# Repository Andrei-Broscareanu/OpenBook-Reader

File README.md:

# 📖 eBook Reader Portabil – ESP32-C6 Edition

Un eBook Reader cu consum redus, afișaj E-Ink și conectivitate modernă (Wi-Fi 6 & Bluetooth 5), construit în jurul microcontrollerului **ESP32-C6-WROOM-1-N8**.

---

## 🔧 Arhitectură Hardware

### 🧠 Microcontroller
- **ESP32-C6-WROOM-1-N8**
  - RISC-V core
  - Wi-Fi 6 și Bluetooth 5
  - Criptografie hardware integrată
  - Interfețe: SPI, I2C, GPIO

### 💾 Memorie
- **64MB NOR Flash** – W25Q512JVEIQ, conectată prin SPI
- **Slot microSD** – pentru stocare eBooks, conectat pe SPI separat

### 🔋 Alimentare
- **USB-C (PMF0501)** – intrare standard 5V
- **Protecție ESD (USBLC6-2SC6Y)** – pentru liniile USB
- **Încărcător Li-Po (MCP73831)** – pentru o celulă 3.7V, max 500mA
- **Baterie Li-Po 3.7V** – autonomie extinsă
- **Regulator LDO (MCP1700-3302E)** – convertește 5V la 3.3V

---

## 🖼️ Afișaj E-Ink

- Conector pentru ecrane de **1.54" E-Paper (200x200px)**
- Interfață: **SPI + GPIO**
- Circuit de alimentare:
  - Transistor Q3
  - Inductor L1
  - Diodă D2
- **Selector SJ1** – pentru tipul de display

---

## 📦 Periferice & Senzori

| Componentă        | Funcție                                | Interfață | Pini ESP32-C6         |
|-------------------|-----------------------------------------|-----------|------------------------|
| **BME688**        | Temperatură, umiditate, presiune, VOCs | I2C       | GPIO1 (SDA), GPIO2 (SCL) |
| **DS3231SN**      | RTC – ceas timp real                   | I2C       | GPIO1 (SDA), GPIO2 (SCL) |
| **MAX17048G-T10** | Fuel gauge baterie                     | I2C       | GPIO1 (SDA), GPIO2 (SCL) |
| **Buton Reset**   | Sistem reset                           | GPIO      | GPIO0                  |
| **Buton Boot**    | Bootloader                             | GPIO      | GPIO3                  |
| **Qwiic/Stemma QT**| Extensii rapide I2C                   | I2C       | GPIO1 (SDA), GPIO2 (SCL) |

---

## 🔌 Pini utilizați pe ESP32-C6

| Componentă       | Interfață     | Pini ESP32-C6             | Observații                |
|------------------|---------------|---------------------------|---------------------------|
| SD Card          | SPI           | GPIO10, GPIO11, GPIO12, GPIO13 | Bus SPI dedicat         |
| NOR Flash        | SPI           | GPIO6, GPIO7, GPIO8, GPIO9      | Bus SPI separat         |
| E-Ink Display    | SPI + GPIO    | GPIO18, GPIO19, GPIO20, GPIO21 | Control ecran           |
| Senzori + RTC    | I2C           | GPIO1 (SDA), GPIO2 (SCL)        | Comun I2C               |
| Butoane sistem   | GPIO          | GPIO0 (RST), GPIO3 (BOOT)       | Control utilizator      |
| Test Pads        | GPIO/UART     | GPIO17, GPIO22                   | Debug/UART              |

---

## ⚡ Estimare consum de energie

| Modul                    | Consum aproximativ         |
|--------------------------|----------------------------|
| ESP32-C6 activ           | ~80-100 mA                 |
| ESP32-C6 deep sleep      | ~10 µA                     |
| E-Ink refresh            | ~25 mA (temporar)          |
| SD Card idle / acces     | ~2 mA / ~50 mA             |
| RTC + BME688 standby     | ~3-5 µA                    |
| MAX17048                 | ~3 µA                      |

**Autonomie estimată cu baterie Li-Po 500mAh:**
- Utilizare normală: **15-20 ore**
- Standby (deep sleep): **până la câteva săptămâni**

---

## 🧩 Design PCB și carcasă

- Blocuri separate: alimentare, MCU, afișaj, senzori
- Plan de masă comun și trasee optimizate
- Conectori accesibili extern (USB, afisaj, butoane)
- Carcasă 3D ergonomică și compactă
- Randări 3D disponibile

---

## ✅ Status proiect

- [x] Hardware complet funcțional
- [x] PCB finalizat și validat
- [x] Carcasă 3D completă
- [x] Optimizare consum energetic
- [x] Conectivitate Wi-Fi 6 și Bluetooth 5

---

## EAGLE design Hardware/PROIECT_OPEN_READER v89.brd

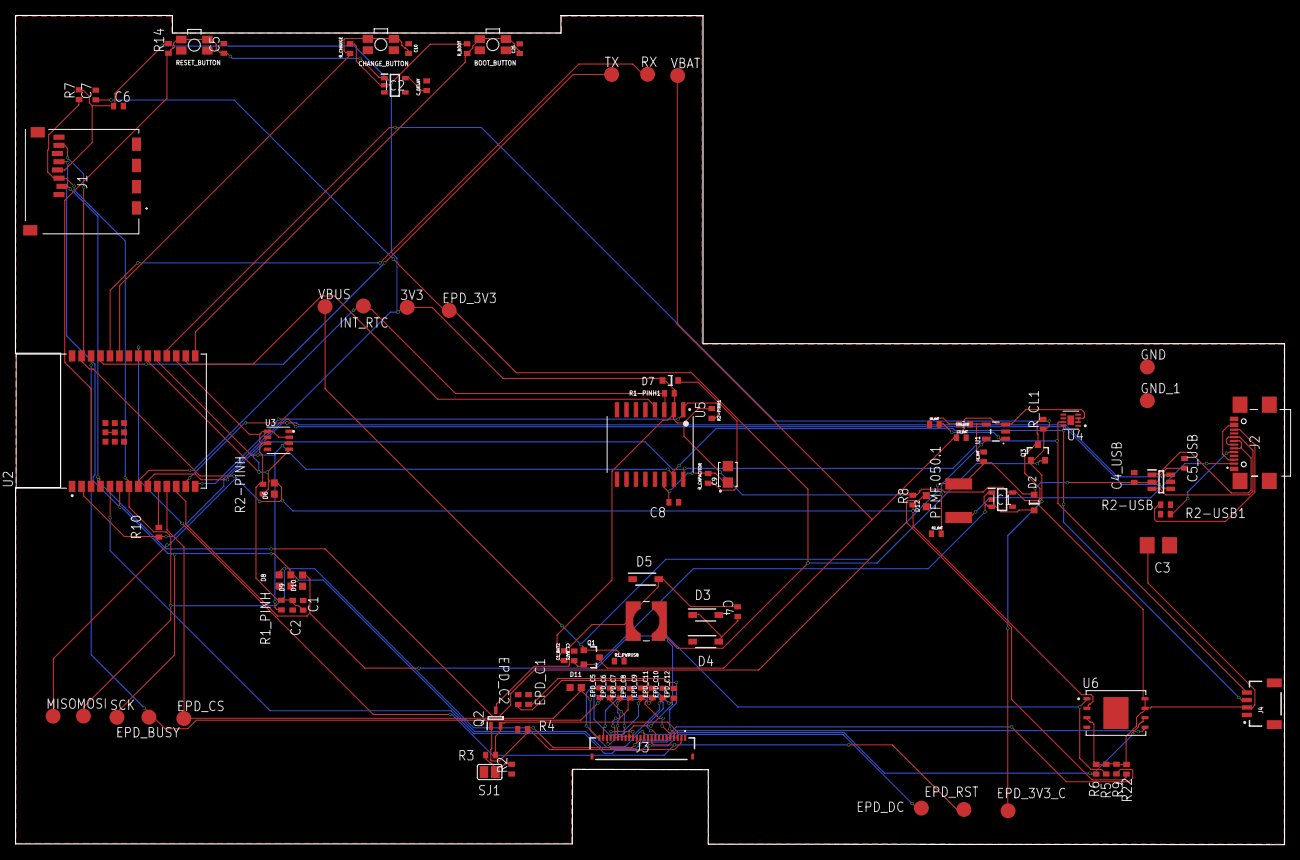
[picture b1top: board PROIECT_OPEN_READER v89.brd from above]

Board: 2 copper layers, 170.2 x 111.2 mm, 103 parts (0 on the bottom side), 57 nets.

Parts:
3V3: TPTP20R; TP20R
BOOT_BUTTON: BUTTON_CUSYOMV1; MYBUTTON
C1, C1_BAT1, C1_BAT2, C2: EAGLE-LTSPICE_C0402
C1_BAT, C2_BAT, C5_USB: 4.7uF; EAGLE-LTSPICE_C0402
C3: RCL_CT3528
C4: 4.7uF/25V; EAGLE-LTSPICE_C0402
C4_USB, C6, C8, C10, C25: 100nF; EAGLE-LTSPICE_C0402
C5: 1uF; EAGLE-LTSPICE_C0402
C7: 10uF; EAGLE-LTSPICE_C0402
C9: CPH3225A; CAPCP3225X100N
CHANGE_BUTTON: BUTTON_CUSYOMV1; MYBUTTON
CHG_LED: ADAFRUIT_CHIP-LED0603
C_DELAY: 100nF; EAGLE-LTSPICE_C0402
D1: USBLC6-2SC6Y; SOT95P280X145-6N
D2, D7: ESP32_WROVER_AVX---SD0805S020S1R0_AVX_SD0805S020S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; ESP32_WROVER_AVX---SD0805S020S1R0_AVX_SD0805S020S1R0_0
D3, D4, D5: MBR0530; SOD3716X135N
D6, D8, D9, D10, D11, D12: PGB1010603MR; DIOC1608X36N
EPD_3V3, EPD_3V3_C: TPTP20R; TP20R
EPD_BUSY: TPTP20R; TP20R
EPD_C1, EPD_C2, EPD_C6, EPD_C7, EPD_C8, EPD_C9, EPD_C10, EPD_C11, EPD_C12: 1uF/50V; EAGLE-LTSPICE_C0402
EPD_C5: 0.1uF/50V; EAGLE-LTSPICE_C0402
EPD_CS: TPTP20R; TP20R
EPD_DC: TPTP20R; TP20R
EPD_RST: TPTP20R; TP20R
GND: TPTP20R; TP20R
GND_1: TPTP20R; TP20R
IC1: XC6220A331MR-G; SOT95P280X120-5N
IC2: BD5229G-TR; SOT95P280X125-5N
INT_RTC: TPTP20R; TP20R
J1: 112A-TAAR-R03_ATTEND; 112ATAARR03ATTEND
J2: SAMACSYS_PARTS_USB4110-GF-A; SAMACSYS_PARTS_USB4110GFA
J3: FH34SRJ-24S-0.5SH_99_; FH34SRJ24S05SH99
J4: QWIIC_RIGHT_ANGLE; JST04_1MM_RA
L1: 68uH; IND_4828-WE-TPC_WRE
MISO: TPTP20R; TP20R
MOSI: TPTP20R; TP20R
PFMF.050.1: ESP32C6_VARISTOR_CT/CN1812
Q1, Q3: 20V/4.2A/52mΩ/1.4W; ESP32_WROVER_SPARKFUN-DISCRETESEMI_SOT23-3
Q2: SI1308EDL-T1-GE3; SOT65P210X110-3N
R1-PINH1, R1_PINH, R2-PINH, R2-PINH1, R4: 10K; ESP32_WROVER_EAGLE-LTSPICE_R0402
R1_BAT: 200; ESP32_WROVER_EAGLE-LTSPICE_R0402
R1_PWRUSB: 100K; ESP32_WROVER_EAGLE-LTSPICE_R0402
R2: 2.2; ESP32_WROVER_EAGLE-LTSPICE_R0402
R2-USB: 5K1; ESP32_WROVER_EAGLE-LTSPICE_R0402
R2-USB1: 5k1; ESP32_WROVER_EAGLE-LTSPICE_R0402
R2_BAT: 2K; ESP32_WROVER_EAGLE-LTSPICE_R0402
R3: 0.47; ESP32_WROVER_EAGLE-LTSPICE_R0402
R5, R6, R7, R8, R9, R14, R22: ESP32_WROVER_EAGLE-LTSPICE_R0402
R10: R1; ESP32_WROVER_EAGLE-LTSPICE_R0402
RESET_BUTTON: BUTTON_CUSYOMV1; MYBUTTON
RX: TPTP20R; TP20R
R_BOOT: 10K; ESP32_WROVER_EAGLE-LTSPICE_R0402
R_CAPACITOR: 15; ESP32_WROVER_EAGLE-LTSPICE_R0402
R_CHANGE: 10K; ESP32_WROVER_EAGLE-LTSPICE_R0402
R_CL1: 10K; ESP32_WROVER_EAGLE-LTSPICE_R0402
SCK: TPTP20R; TP20R
SJ1: SJ
TX: TPTP20R; TP20R
U1: ESP32_WROVER_SPARKFUN-IC-POWER_SOT23-5
U2: ESP32-C6-WROOM-1-N8; XCVR_ESP32-C6-WROOM-1-N8
U3: ESP32_WROVER_BME680_BME680; ESP32_WROVER_BME680_PSON80P300X300X100-8N
U4: MAX17048G+T10; SON50P200X200X80-9N
U5: DS3231SN#; SOIC127P1032X265-16N
U6: W25Q512JVEIQ; SON127P600X800X80-9N
VBAT: TPTP20R; TP20R
VBUS: TPTP20R; TP20R

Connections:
3V3: 3V3.TP, C1_BAT2.1, C3.+, C6.1, D7.2, IC1.5, IC2.2, J1.P4, J4.2, Q3.3, R1-PINH1.2, R2-PINH1.2, R5.2, R6.2, R7.2, R8.2, R9.2, R10.1, R14.2, R22.2, R_BOOT.2, R_CHANGE.2, R_CL1.2, U2.2, U5.2, U6.3, U6.7, U6.8
32KHZ: R2-PINH1.1, U2.9, U5.1
DN: D1.1, J2.A7, J2.B7
DP: D1.3, J2.A6, J2.B6
EPD_3V3: C7.1, EPD_3V3.TP, J3.16, L1.2, Q3.2
EPD_3V3_C: EPD_3V3_C.TP, Q3.1, R_CL1.1, U2.18
EPD_BUSY: EPD_BUSY.TP, J3.9, U2.26
EPD_CS: D11.2, EPD_CS.TP, J3.12, R9.1, U2.11
EPD_DC: EPD_DC.TP, J3.11, U2.5
EPD_RST: EPD_RST.TP, J3.10, U2.21
FLASH_CS: D10.2, R5.1, U2.12, U6.1
GDR: J3.2, Q2.1, R4.2
GND: BOOT_BUTTON.1, BOOT_BUTTON.2, C1.2, C1_BAT.2, C1_BAT1.2, C1_BAT2.2, C2.2, C2_BAT.2, C3.-, C4_USB.2, C5.2, C5_USB.2, C6.2, C7.2, C8.2, C9.2, C10.2, C25.2, CHANGE_BUTTON.1, CHANGE_BUTTON.2, C_DELAY.2, D1.5, D4.1, D6.1, D8.1, D9.1, D10.1, D11.1, D12.1, EPD_C1.2, EPD_C2.2, EPD_C5.1, EPD_C6.2, EPD_C7.2, EPD_C8.2, EPD_C9.2, EPD_C10.2, EPD_C11.2, EPD_C12.2, GND.TP, GND_1.TP, IC1.2, IC2.3, J1.G1, J1.G2, J1.G3, J1.G4, J1.P6, J2.A1, J2.A12, J2.B1, J2.B12, J2.MP1, J2.MP2, J2.MP3, J2.MP4, J3.8, J3.17, J3.MP1, J3.MP2, J4.1, R1_PWRUSB.1, R2.1, R2-USB.2, R2-USB1.1, R2_BAT.1, R4.1, RESET_BUTTON.1, RESET_BUTTON.2, SJ1.1, U1.2, U2.1, U2.28, U2.29_1, U2.29_2, U2.29_3, U2.29_4, U2.29_5, U2.29_6, U2.29_7, U2.29_8, U2.29_9, U3.1, U3.5, U3.7, U4.1, U4.4, U4.6, U4.9, U5.13, U6.4, U6.9
GPIO8: R10.2, U2.10
I2C_PW: C1.1, C2.1, R1_PINH.2, R2-PINH.2, U2.17, U3.2, U3.6, U3.8
INT_RTC: INT_RTC.TP, R1-PINH1.1, U2.8, U5.3
IO/BOOT: BOOT_BUTTON.3, BOOT_BUTTON.4, C25.1, R_BOOT.1, U2.15
IO/CHANGE: C10.1, CHANGE_BUTTON.3, CHANGE_BUTTON.4, R_CHANGE.1, U2.23
MISO: D6.2, J1.P7, MISO.TP, R8.1, U2.27, U6.2
MOSI: D8.2, J1.P3, J3.14, MOSI.TP, R7.1, U2.7, U6.5
unnamed: J2.A4, PFMF.050.1.1
unnamed: J2.A5, R2-USB1.2
unnamed: J2.B5, R2-USB.1
unnamed: C1_BAT1.1, D2.1, IC1.1, IC1.3, Q1.2
unnamed: EPD_C12.1, J3.24
unnamed: EPD_C11.1, J3.23
unnamed: C4.1, D3.1, D4.2
unnamed: R2_BAT.2, U1.5
unnamed: EPD_C10.1, J3.22
unnamed: EPD_C9.1, J3.21
unnamed: CHG_LED.C, R1_BAT.1
unnamed: R1_BAT.2, U1.1
unnamed: EPD_C8.1, J3.20
unnamed: EPD_C7.1, J3.19
unnamed: EPD_C6.1, J3.18
unnamed: C_DELAY.1, IC2.5
unnamed: EPD_C5.2, J3.15
unnamed: EPD_C2.1, J3.5
unnamed: EPD_C1.1, J3.4
unnamed: D7.1, R_CAPACITOR.1
RESE: J3.3, Q2.2, R3.2
RESE': R2.2, R3.1, SJ1.2
RESET: C5.1, IC2.1, R14.1, RESET_BUTTON.3, RESET_BUTTON.4, U2.3
RTC_RST: U2.16, U5.4
RX: RX.TP, U2.24
SCK: D9.2, J1.P5, J3.13, R6.1, SCK.TP, U2.6, U6.6
SCL: J4.4, R2-PINH.1, U2.20, U3.4, U4.7, U5.16
SDA: J4.3, R1_PINH.1, U2.19, U3.3, U4.8, U5.15
SRC: C4.2, D5.2, L1.1, Q2.3
SS_SD: D12.2, J1.P2, R22.1, U2.4
TX: TX.TP, U2.25
USB_D+: D1.4, U2.14
USB_D-: D1.6, U2.13
VBAT: C2_BAT.1, Q1.3, U1.3, U4.2, U4.3, VBAT.TP
VBUS: C1_BAT.1, C4_USB.1, C5_USB.1, CHG_LED.A, D1.2, D2.2, PFMF.050.1.2, Q1.1, R1_PWRUSB.2, U1.4, VBUS.TP
VRTC: C8.1, C9.1, R_CAPACITOR.2, U5.14
VUSB: J2.A9, J2.B4, J2.B9

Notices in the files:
parts and their libraries:
COPYRIGHT: Copyright (C) 2024 Ultra Librarian. All rights reserved.
